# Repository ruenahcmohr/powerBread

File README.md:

# powerBread
Molex power adapter for breadboards.

** I do not use this with a high current power supply **

And I OFTEN short the rails, so I'm glad I dont.
There is no current protection on this board, so be careful.

The top rail is configurable between 5 or 12V. The power led comes off this configurable rail, so make sure the LED resistor value is good for 12V, its intentional that it be dimmer at 5V, gies you a clue what voltage your set to.

The bottom rails has an extra two pins on the left. THESE PINS GO UP!!! They are meant for clipping alligator clips to for grounds, not going into the breadboard. 

The resistor and LED are 0805 surface mount parts (YOU CAN DO IT!) 

I use this with molex connectors like (hopefully this link lives a while) https://vi.aliexpress.com/item/1005005555699253.html

photos of my old one as a refrence:

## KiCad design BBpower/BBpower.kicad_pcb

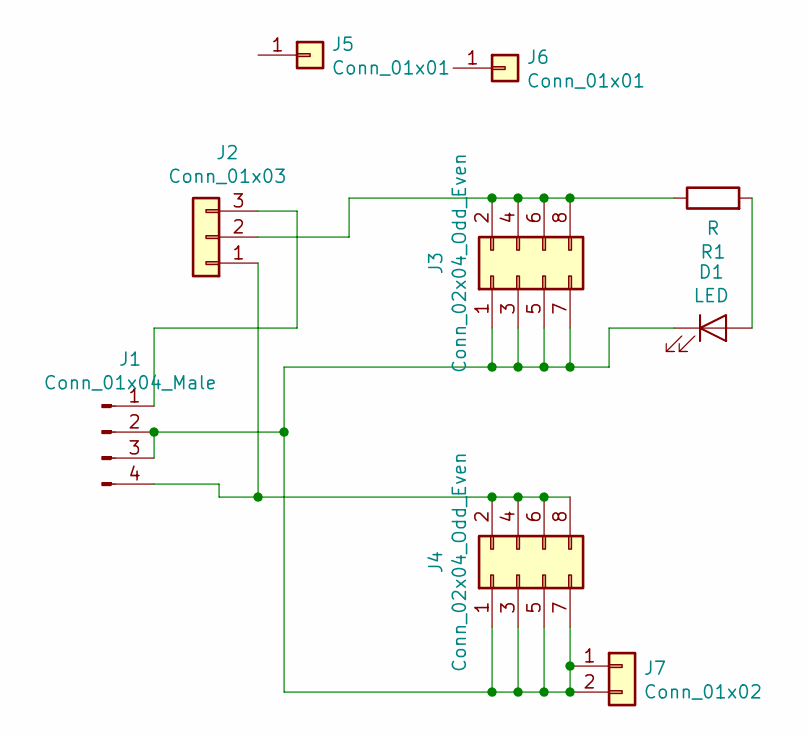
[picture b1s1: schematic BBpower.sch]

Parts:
D1: LED; LED_0805_2012Metric
J1: Conn_01x04_Male; PhoenixContact_MSTBA_2,5_4-G-5,08_1x04_P5.08mm_Horizontal
J2: Conn_01x03; PinHeader_1x03_P2.54mm_Vertical
J3, J4: Conn_02x04_Odd_Even; PinHeader_2x04_P2.54mm_Vertical
J5, J6: Conn_01x01; PinHeader_1x01_P2.54mm_Vertical
J7: Conn_01x02; PinHeader_2x01_P2.54mm_Vertical
R1: R; R_0805_2012Metric

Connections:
unnamed: D1.1 (K), J1.2, J1.3, J3.1, J3.3, J3.5, J3.7, J4.1, J4.3, J4.5, J4.7, J7.1, J7.2
unnamed: D1.2 (A), R1.2
unnamed: J1.1, J2.3
unnamed: J1.4, J2.1, J4.2, J4.4, J4.6, J4.8
unnamed: J2.2, J3.2, J3.4, J3.6, J3.8, R1.1

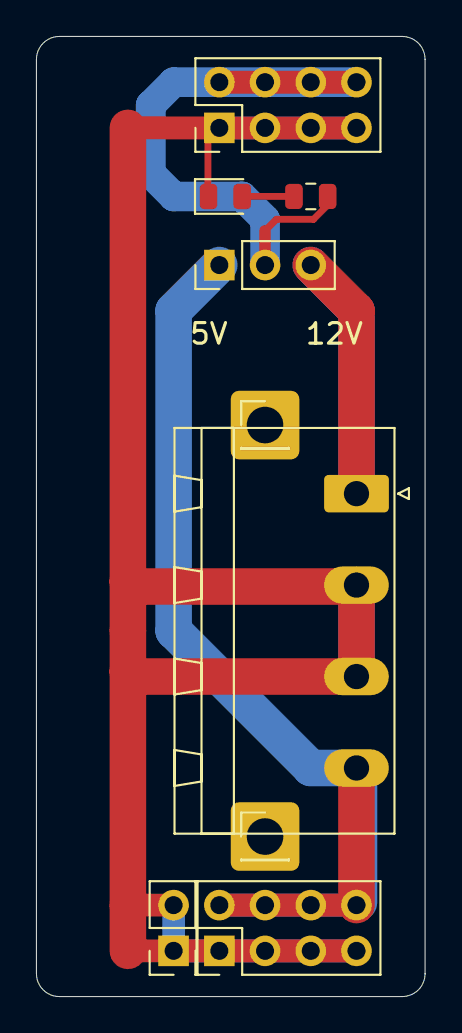
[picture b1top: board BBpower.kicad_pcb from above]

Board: 2 copper layers, 21.6 x 53.3 mm, 9 parts (0 on the bottom side), 5 nets.

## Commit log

2024-05-05 adding files
